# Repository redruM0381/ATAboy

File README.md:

If you don't want to build your own, the hardware can be purchased here:  https://obsoletetech.us/products/ataboy-an-open-source-legacy-ide-usb-bridge

-----------------------------------------------------------------------------------

ATAboy is designed for retro computing enthusiasts, data recovery experts, and archivists.  Read and write the oldest of IDE hard drives, without the need for an "in-between" vintage computer!

ATAboy is a user-friendly bridge that allows classic IDE (PATA) hard drives to be connected to a modern computer over USB as a standard USB Mass Storage device.  While cheap, modern adapters usually only work with newer "LBA" type drives, ATAboy works all the way back to the earliest CHS only, PIO Mode 0, ATA disks.  (It will also work with newer LBA type IDE disks, but that's not really what it's designed for.)  ATAboy features an "Award BIOS inspired" user friendly UI for drive configuration and setup.

---

When connected:

* The IDE drive appears to your computer like a normal USB Mass Storage Device
* No special drivers are required (Windows, Linux, macOS supported)
* The device translates USB Mass Storage commands into IDE read/write operations

---

## Hardware Requirements

To get started, you will also need:

* Any 40‑pin IDE (PATA) hard drive. It may be jumpered master, slave, or cable select.
* An external PSU to power the drive.
* A USB-C cable to connect ATAboy to the host computer.
* Any standard ANSI compatible serial terminal emulator (e.g. PuTTY, Tera Term, minicom, screen, etc.)

---

## Basic drive mount using ATABoy

1. Connect the IDE ribbon cable to the drive and ATAboy (Note Pin 1 orientation, usually marked by a stripe on the cable)
2. Power the drive using external supply
3. Connect ATAboy to your computer via USB
4. Connect to serial console with terminal of choice ([PuTTY](https://www.chiark.greenend.org.uk/~sgtatham/putty/latest.html) shown).  9600 8N1, no flow control.  You should see an Award BIOS "inspired" text-based UI appear in the terminal.
5. Enter the "Auto Detect & Set Geometry" menu
6. Choose default, or enter geometry manually if needed
7. Choose "Mount HDD to USB Mass Storage"
8. That's it!  You can now read the drive from your modern OS!

---

You can save the current ATAboy settings, geometry, etc to EEPROM, which will be restored the next time the device is booted.  (This allows auto-mounting also.)

IMPORTANT!  If you are working with valuable or irreplaceable data, ensure write protection is enabled before mounting.  It is enabled by default for safety.  You do NOT want the host OS to touch or bless the disk!
Windows VDS/RPC services can often crash if it is unable to write to a drive with damaged/legacy MBR and/or partition tables.
This can result in various Windows errors, unable to mount the drive, etc.  However, raw data can usually still be accessed via dd, or other raw disk backup software.
Regardless, it is STRONGLY recommended the entire drive be dumped to an image file BEFORE disabling write protection, then mounting the drive in Explorer.

---

## Safe Removal

Always use your operating system’s **Safely Remove / Eject** feature before:

* Unplugging the USB cable
* Powering off the IDE drive

This helps prevent:

* File system corruption
* Incomplete writes
* OS-side errors

---

## Known Limitations

ATAboy is a hobbyist and experimental project. You should be aware that:

* Performance is significantly slower than modern USB to IDE bridges.  We're working over USB 1.1 for now.  This can cause long mount times, especially in Windows if the disk has file system weirdness.
* Many legacy disks use unusual geometry, and may require experimentation.
* Not all OS disk utilities behave the same way

# PLEASE NOTE!
Some of the firmware code was written with AI assistance.  It has been tested with dozens of drives, and does function well with most.  But may be buggy, slow, or unresponsive with certain drives. Please let us know if you find a drive that does or doesn't work right. We'll build a compatibilty list soon.
# Use at your own risk!

* Firmware written in VS Code with Raspberry Pi Pico Extension
* PCB designed in Kicad
* Case designed in Freecad

---

ATAboy is meant to be hacked, learned from, and improved.
Have fun, and thank you for trying ATAboy!

# Licensing

"ATAboy" is a trademark of JJ Dasher.
The open source licenses do not grant rights to use these trademarks.

## Firmware
Licensed under GNU GPLv3.
See /firmware/LICENSE.

## Hardware
Licensed under CERN-OHL-W v2.
See /PCB/LICENSE.

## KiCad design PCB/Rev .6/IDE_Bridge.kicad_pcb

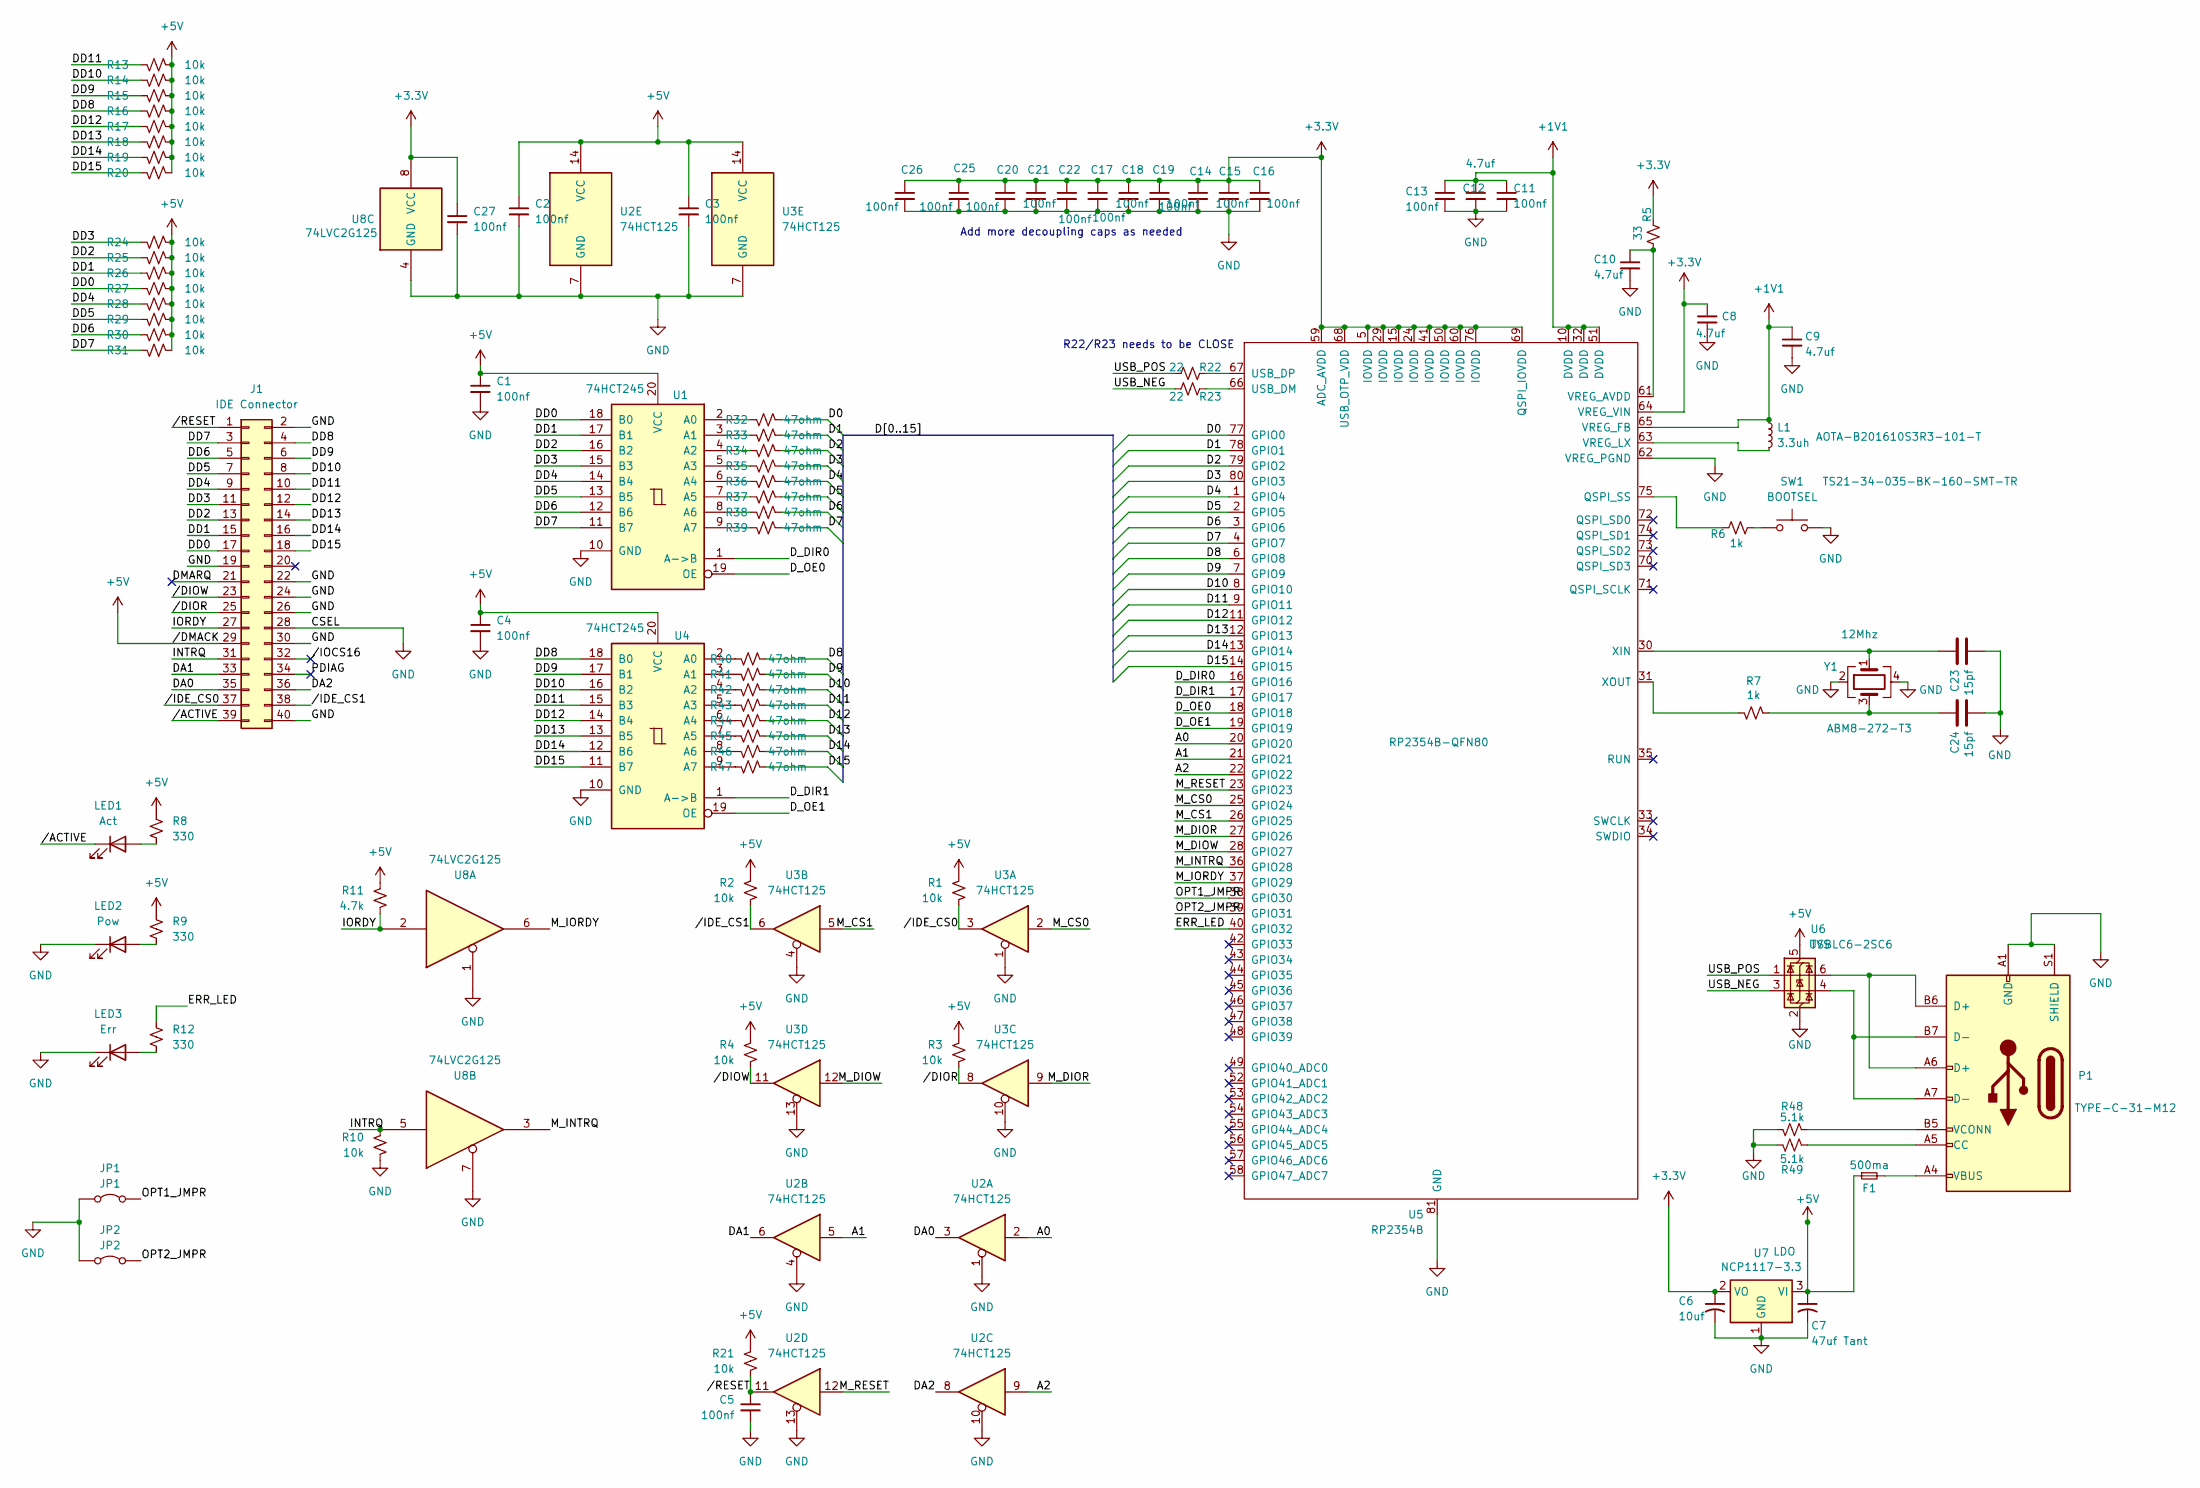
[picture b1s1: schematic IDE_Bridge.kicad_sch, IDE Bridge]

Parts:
C1, C2, C3, C4, C5, C11, C13, C14, C15, C16, C17, C18, C19, C20, C21, C22, C25, C26, C27: 100nf; C_0402_1005Metric; LCSC C1525
C6: 10uf; C_1206_3216Metric; LCSC C13585
C7: 47uf Tant; CP_EIA-6032-28_Kemet-C; LCSC C7219
C8, C9, C10, C12: 4.7uf; C_0402_1005Metric; LCSC C23733
C23, C24: 15pf; C_0402_1005Metric; LCSC C1548
F1: 500ma; Fuse_0805_2012Metric; LCSC C22435710
J1: IDE Connector; PinHeader_2x20_P2.54mm_Horizontal
JP1: JP1; PinHeader_1x02_P2.54mm_Vertical
JP2: JP2; PinHeader_1x02_P2.54mm_Vertical
L1: 3.3uh; L_Murata_DFE201610P; LCSC C42411119
LED1: Act; LED_0805_2012Metric; LCSC C2296
LED2: Pow; LED_0805_2012Metric; LCSC C2297
LED3: Err; LED_0805_2012Metric; LCSC C84256
P1: USB_C_Plug_USB2.0; USB_C_Receptacle_HRO_TYPE-C-31-M-12; LCSC C165948
R1, R2, R3, R4, R10, R13, R14, R15, R16, R17, R18, R19, R20, R21, R24, R25, R26, R27, R28, R29, R30, R31: 10k; R_0402_1005Metric; LCSC C25744
R5: 33; R_0402_1005Metric; LCSC C25105
R6, R7: 1k; R_0402_1005Metric; LCSC C11702
R8, R9, R12: 330; R_0402_1005Metric; LCSC C25104
R11: 4.7k; R_0402_1005Metric; LCSC C25900
R22, R23: 22; R_0402_1005Metric; LCSC C25092
R32, R33, R34, R35, R36, R37, R38, R39, R40, R41, R42, R43, R44, R45, R46, R47: 47ohm; R_0402_1005Metric; LCSC C25118
R48, R49: 5.1k; R_0402_1005Metric; LCSC C25905
SW1: BOOTSEL; SW_SPST_SKQG_WithStem; LCSC C318884
U1, U4: 74HCT245; SOIC-20W_7.5x12.8mm_P1.27mm; LCSC C5625
U2, U3: 74HCT125; SOIC-14_3.9x8.7mm_P1.27mm; LCSC C352957
U5: RP2354B; RP2350B; LCSC C39843328
U6: TVS; SOT-23-6; LCSC C2687116
U7: LDO; SOT-223-3_TabPin2; LCSC C6186
U8: 74LVC2G125; VSSOP-8_3x3mm_P0.65mm; LCSC C206035
Y1: 12Mhz; Crystal_SMD_3225-4Pin_3.2x2.5mm; LCSC C20625731

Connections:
+1V1: C9.1, C11.1, C12.1, C13.1, L1.1, U5.10 (DVDD), U5.32 (DVDD), U5.51 (DVDD), U5.65 (VREG_FB)
+3.3V: C6.1, C8.1, C14.1, C15.1, C16.1, C17.1, C18.1, C19.1, C20.1, C21.1, C22.1, C25.1, C26.1, C27.1, R5.2, U5.5 (IOVDD), U5.15 (IOVDD), U5.24 (IOVDD), U5.29 (IOVDD), U5.41 (IOVDD), U5.50 (IOVDD), U5.59 (ADC_AVDD), U5.60 (IOVDD), U5.64 (VREG_VIN), U5.68 (USB_OTP_VDD), U5.69 (QSPI_IOVDD), U5.76 (IOVDD), U7.2 (VO), U8.8 (VCC)
+5V: C1.1, C2.1, C3.1, C4.1, C7.1, F1.1, J1.29, R1.1, R2.1, R3.1, R4.1, R8.1, R9.1, R11.1, R13.2, R14.2, R15.2, R16.2, R17.2, R18.2, R19.2, R20.2, R21.1, R24.2, R25.2, R26.2, R27.2, R28.2, R29.2, R30.2, R31.2, U1.20 (VCC), U2.14 (VCC), U3.14 (VCC), U4.20 (VCC), U6.5 (VBUS), U7.3 (VI)
/A0: U2.2, U5.20 (GPIO20)
/A1: U2.5, U5.21 (GPIO21)
/A2: U2.9, U5.22 (GPIO22)
/D0: R32.2, U5.77 (GPIO0)
/D1: R33.2, U5.78 (GPIO1)
/D2: R34.2, U5.79 (GPIO2)
/D3: R35.2, U5.80 (GPIO3)
/D4: R36.2, U5.1 (GPIO4)
/D5: R37.2, U5.2 (GPIO5)
/D6: R38.2, U5.3 (GPIO6)
/D7: R39.2, U5.4 (GPIO7)
/D8: R40.2, U5.6 (GPIO8)
/D9: R41.2, U5.7 (GPIO9)
/D10: R42.2, U5.8 (GPIO10)
/D11: R43.2, U5.9 (GPIO11)
/D12: R44.2, U5.11 (GPIO12)
/D13: R45.2, U5.12 (GPIO13)
/D14: R46.2, U5.13 (GPIO14)
/D15: R47.2, U5.14 (GPIO15)
/DA0: J1.35, U2.3
/DA1: J1.33, U2.6
/DA2: J1.36, U2.8
/DD0: J1.17, R27.1, U1.18 (B0)
/DD1: J1.15, R26.1, U1.17 (B1)
/DD2: J1.13, R25.1, U1.16 (B2)
/DD3: J1.11, R24.1, U1.15 (B3)
/DD4: J1.9, R28.1, U1.14 (B4)
/DD5: J1.7, R29.1, U1.13 (B5)
/DD6: J1.5, R30.1, U1.12 (B6)
/DD7: J1.3, R31.1, U1.11 (B7)
/DD8: J1.4, R16.1, U4.18 (B0)
/DD9: J1.6, R15.1, U4.17 (B1)
/DD10: J1.8, R14.1, U4.16 (B2)
/DD11: J1.10, R13.1, U4.15 (B3)
/DD12: J1.12, R17.1, U4.14 (B4)
/DD13: J1.14, R18.1, U4.13 (B5)
/DD14: J1.16, R19.1, U4.12 (B6)
/DD15: J1.18, R20.1, U4.11 (B7)
/DMARQ: J1.21
/D_DIR0: U1.1 (A->B), U5.16 (GPIO16)
/D_DIR1: U4.1 (A->B), U5.17 (GPIO17)
/D_OE0: U1.19 (OE), U5.18 (GPIO18)
/D_OE1: U4.19 (OE), U5.19 (GPIO19)
/ERR_LED: R12.1, U5.40 (GPIO32)
/INTRQ: J1.31, R10.1, U8.5
/IORDY: J1.27, R11.2, U8.2
/M_CS0: U3.2, U5.25 (GPIO24)
/M_CS1: U3.5, U5.26 (GPIO25)
/M_DIOR: U3.9, U5.27 (GPIO26)
/M_DIOW: U3.12, U5.28 (GPIO27)
/M_INTRQ: U5.36 (GPIO28), U8.3
/M_IORDY: U5.37 (GPIO29), U8.6
/M_RESET: U2.12, U5.23 (GPIO23)
/OPT1_JMPR: JP1.2 (B), U5.38 (GPIO30)
/OPT2_JMPR: JP2.2 (B), U5.39 (GPIO31)
/PDIAG: J1.34
/USB_NEG: R23.1, U6.3 (I/O2)
/USB_POS: R22.1, U6.1 (I/O1)
//ACTIVE: J1.39, LED1.1 (K)
//DIOR: J1.25, R3.2, U3.8
//DIOW: J1.23, R4.2, U3.11
//IDE_CS0: J1.37, R1.2, U3.3
//IDE_CS1: J1.38, R2.2, U3.6
//IOCS16: J1.32
//RESET: C5.1, J1.1, R21.2, U2.11
GND: C1.2, C2.2, C3.2, C4.2, C5.2, C6.2, C7.2, C8.2, C9.2, C10.2, C11.2, C12.2, C13.2, C14.2, C15.2, C16.2, C17.2, C18.2, C19.2, C20.2, C21.2, C22.2, C23.2, C24.2, C25.2, C26.2, C27.2, J1.2, J1.19, J1.22, J1.24, J1.26, J1.28, J1.30, J1.40, JP1.1 (A), JP2.1 (A), LED2.1 (K), LED3.1 (K), P1.A1 (GND), P1.A12 (GND), P1.B1 (GND), P1.B12 (GND), P1.S1 (SHIELD), R10.2, R48.1, R49.1, SW1.2, U1.10 (GND), U2.1, U2.4, U2.7 (GND), U2.10, U2.13, U3.1, U3.4, U3.7 (GND), U3.10, U3.13, U4.10 (GND), U5.62 (VREG_PGND), U5.81 (GND), U6.2 (GND), U7.1 (GND), U8.1, U8.4 (GND), U8.7, Y1.2, Y1.4
unnamed: C24.1, R7.2, Y1.3
unnamed: F1.2, P1.A4 (VBUS), P1.A9 (VBUS), P1.B4 (VBUS), P1.B9 (VBUS)
unnamed: LED1.2 (A), R8.2
unnamed: LED2.2 (A), R9.2
unnamed: LED3.2 (A), R12.2
unnamed: P1.A5 (CC), R49.2
unnamed: P1.A6 (D+), P1.B6 (D+), U6.6 (I/O1)
unnamed: P1.A7 (D-), P1.B7 (D-), U6.4 (I/O2)
unnamed: P1.B5 (VCONN), R48.2
unnamed: R6.1, SW1.1
unnamed: R32.1, U1.2 (A0)
unnamed: R33.1, U1.3 (A1)
unnamed: R34.1, U1.4 (A2)
unnamed: R35.1, U1.5 (A3)
unnamed: R36.1, U1.6 (A4)
unnamed: R37.1, U1.7 (A5)
unnamed: R38.1, U1.8 (A6)
unnamed: R39.1, U1.9 (A7)
unnamed: R40.1, U4.2 (A0)
unnamed: R41.1, U4.3 (A1)
unnamed: R42.1, U4.4 (A2)
unnamed: R43.1, U4.5 (A3)
unnamed: R44.1, U4.6 (A4)
unnamed: R45.1, U4.7 (A5)
unnamed: R46.1, U4.8 (A6)
unnamed: R47.1, U4.9 (A7)
unnamed: R6.2, U5.75 (QSPI_SS)
unnamed: R23.2, U5.66 (USB_DM)
unnamed: R22.2, U5.67 (USB_DP)
unnamed: C10.1, R5.1, U5.61 (VREG_AVDD)
unnamed: L1.2, U5.63 (VREG_LX)
unnamed: C23.1, U5.30 (XIN), Y1.1
unnamed: R7.1, U5.31 (XOUT)

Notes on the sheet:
Add more decoupling caps as needed
R22/R23 needs to be CLOSE

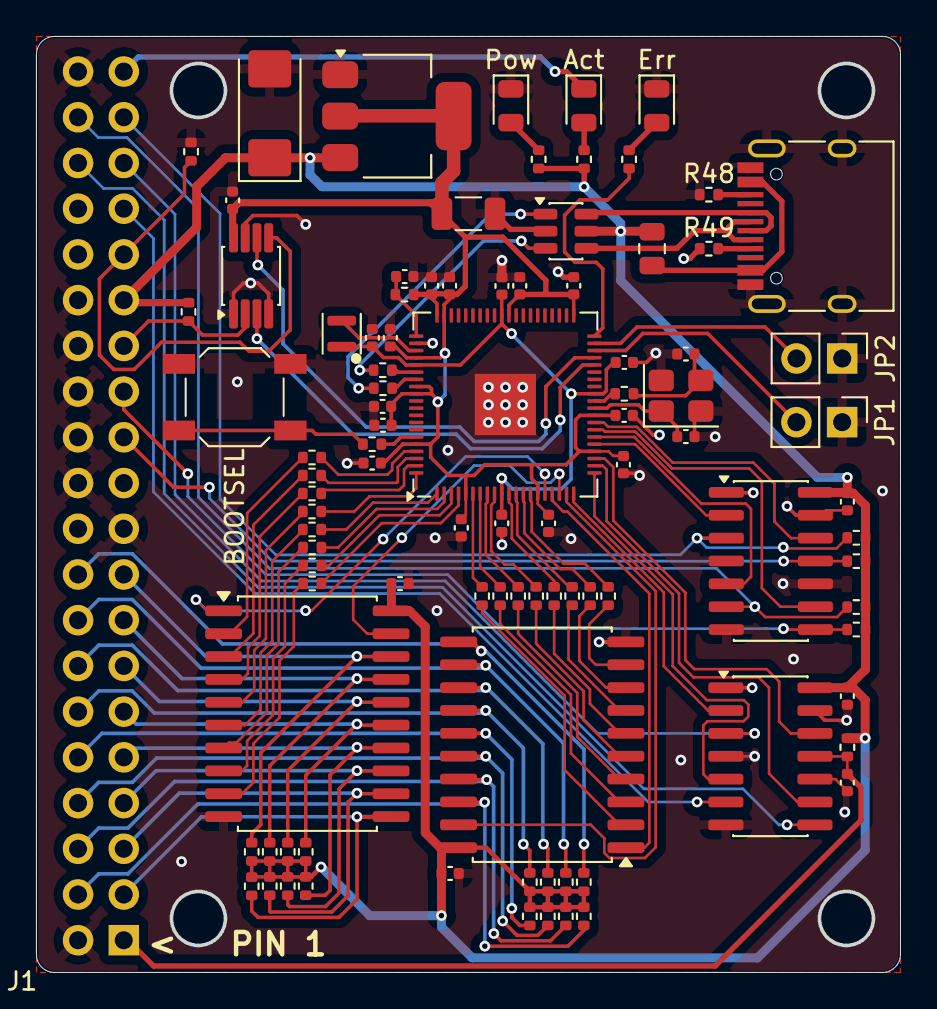
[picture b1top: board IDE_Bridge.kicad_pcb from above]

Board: 2 copper layers, 47.9 x 51.9 mm, 95 parts (0 on the bottom side), 99 nets.

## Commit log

2026-01-09 Delete PCB/files.txt
    no need
2026-01-12 Add files via upload
    Lots of bug fixes
2026-01-12 Add feedback on firmware review and suggested improvements
    Provided detailed feedback on firmware review, highlighting critical issues and recommended fixes for TinyUSB usage, timeout handling, and IDE operations.
2026-01-12 Add detailed review of IDEasy firmware project
    Document the analysis and review of the IDEasy firmware project, including strengths, weaknesses, and suggested improvements across core files like ide_logic.cpp, msc_disk.c, and menus.c.
2026-01-12 Update feedback with corrections and improvement suggestions
    Corrected earlier feedback regarding timeout logic, drive detection, reset implementation, SCSI sense code reporting, and debug logging. Highlighted areas for improvement, including read-cache invali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
2026-01-31 Delete bugged directory
    Cleaning up
2026-01-31 Delete PCB directory
    Noit ready to share yet
2026-01-31 Delete usb_descriptors.c
    Cleaning up
2026-01-31 Delete tusb_config.h
    Cleaning up
2026-02-01 Delete pico_sdk_import.cmake
    Cleaning up
2026-02-01 Delete ide_logic.cpp
    Cleaning up
2026-02-01 Delete README.md
    Cleaning up
2026-02-01 Delete CMakeLists.txt
    Cleaning up
2026-02-01 Delete .gitignore
    Cleaning up
2026-02-01 Update README.md
    Cleaning up
2026-02-06 Update README.md
    Updating the name
2026-02-06 Add files via upload
    Renaming project from IDEasy to ATAboy
2026-02-06 Add files via upload
    Updating to new name.
2026-02-16 Rename lid-LidArrow.stl to lid_vert_header.stl
2026-02-16 Rename lid.FCStd to lid_vert_header.FCStd
2026-02-16 Rename ataboycase2.FCStd to case_vert_header.FCStd
2026-02-16 Rename test2.png to logo.png
2026-02-17 Create LICENSE
2026-02-17 Update LICENSE
2026-02-19 Rename ataboy lid vert shroud.stl to lid_vert_shroud.stl
2026-02-19 Rename ataboy lid vert shroud.FCStd to lid_vert_shroud.FCStd
2026-02-19 Rename ataboy case vert shroud.stl to case_vert_shroud.stl
2026-02-19 Rename ataboy case vert shroud.FCStd to case_vert_shroud.FCStd
2026-02-21 Update README.md
    Clarity.
2026-02-21 Update README.md
    Hardware purchase link
2026-02-21 Update README.md
    Moved disclaimer to bottom.
2026-02-24 Rename ATAboy.uf2 to Binary/ATAboy.uf2
2026-02-24 Update README.md
    Added link to putty
2026-02-24 Update README.md
    Cleaned up instructions a bit
2026-02-27 Rename ataboy lid angle shroud.stl to lid_angled_shroud.stl
2026-02-27 Rename ataboy lid angle shroud.FCStd to lid_angled_shroud.FCStd
2026-02-27 Rename ataboy case angle shroud.stl to case_angled_shroud.stl
2026-02-27 Rename ataboy case angle shroud.FCStd to case_angled_shroud.FCStd
2026-03-25 Rename ATAboy.uf2 to ATAboy_05.uf2
2026-03-25 Add files via upload
    New firmware!
2026-03-25 Rename ATAboy.uf2 to ATAboy_v06b.uf2
2026-03-25 Rename firmware/CMakeLists.txt to firmware/.05/CMakeLists.txt
2026-03-25 Rename firmware/.05/CMakeLists.txt to firmware v.05/CMakeLists.txt
2026-03-25 Rename LICENSE to LICENSE
2026-03-25 Rename ide_logic.cpp to ide_logic.cpp
2026-03-25 Rename ide_logic.h to ide_logic.h
2026-03-25 Rename menus.c to menus.c
2026-03-25 Rename msc_disk.c to msc_disk.c
2026-03-25 Rename pico_sdk_import.cmake to pico_sdk_import.cmake
2026-03-25 Rename tusb_config.h to tusb_config.h
2026-03-25 Rename usb_descriptors.c to usb_descriptors.c
2026-03-25 Create test
2026-03-25 Add files via upload
    Version 0.6b released!
    Refactor and overhaul of ATA handling using PIO state machines instead of sloppy timing loops. Huge increase in performance and compatibility. Timing mode removed, as it is no longer needed. Many bug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
2026-03-25 Rename ATAboy_05.uf2 to ATAboy_05.uf2
2026-03-25 Rename ATAboy_v06b.uf2 to ATAboy_v06b.uf2
2026-03-27 Add files via upload
    Many more fixes.
2026-03-27 Rename ATAboy_05.uf2 to ATAboy05.uf2
2026-03-27 Rename ATAboy_v06b.uf2 to ATAboy6b.uf2
2026-03-27 Rename ATAboy05.uf2 to ATAboy5.uf2
2026-03-27 Rename binaries/ATAboy5.uf2 to binaries/older/ATAboy5.uf2
2026-03-27 Rename binaries/ATAboy6b.uf2 to binaries/older/ATAboy6b.uf2
2026-03-27 Rename ATAboy.c to FW source v.6d1/ATAboy.c
2026-03-27 Rename CMakeLists.txt to FW source v.6d1/CMakeLists.txt
2026-03-27 Rename ataboy.pio to FW source v.6d1/ataboy.pio
2026-03-27 Rename config.c to FW source v.6d1/config.c
2026-03-27 Rename config.h to FW source v.6d1/config.h
2026-03-27 Rename ide.c to FW source v.6d1/ide.c
2026-03-27 Rename ide.h to FW source v.6d1/ide.h
2026-03-27 Rename ide_pio.c to FW source v.6d1/ide_pio.c
2026-03-27 Rename ide_pio.h to FW source v.6d1/ide_pio.h
2026-03-27 Rename menus.c to FW source v.6d1/menus.c
2026-03-27 Rename tusb_config.h to FW source v.6d1/tusb_config.h
2026-03-27 Rename usb.c to FW source v.6d1/usb.c
2026-03-27 Rename usb_descriptors.c to FW source v.6d1/usb_descriptors.c
2026-04-02 A slew of fixes and new features
    Ver .6f2 (changes since .6d1)
    Fixed erroneously swapped IORDY/INTRQ GPIOs.
    Now sends 10h recalibrate during reset.
    91h is re-asserted If drive self resets due to UNC or other error, so we can attempt retry.
    Now scans master/slave, and works regardless of jumpering.
    If register responds, but IDENTIFY fails, allows user to force geometry and continue anyway.
2026-04-02 LBA48 bug fix
    LBA48 had a bug. Disks over 132GB should work now.
2026-04-03 Add files via upload
    Added help file
2026-04-08 Updated PCB
    Rev .6 of PCB: FIxed USB-C connector position, and added 5.1k pulldowns for CC1/CC2
2026-04-08 Update PCB
    Rev .6 fixes USB-C connector placement, and adds 2x 5.1k pulldowns for CC lines.
2026-04-26 Update README.md
    Removed master jumper requirement.

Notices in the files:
PCB/Rev .6/IDE_Bridge.kicad_pcb:
© 2026
